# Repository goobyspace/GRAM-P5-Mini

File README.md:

# GRAM Slim

# Brook Version

This repo contains within the folder Gram FGC -> v1.brook, an edited version based on the v1.2 version that uses a brook P5-mini board. It's also edited specifically for a layout I find more comfortable, with the thumb button on the right hand outwards, instead of tucked under.

The PCB was made with heavy inspiration of the V1.2 PCB by [Quark](https://twitter.com/quark_works) as well as the (Flatbox)[https://github.com/jfedor2/flatbox], which includes an example of a Brook mini PCB & it's footprint in the rev3 version. Although the flatbox uses the PS3/PS4 mini, the pinout for the P5 mini has stayed the same.

This project was entirely for my own personal reasons, wanting the split thumb buttons & the pinky buttons on both sides moved down, as well as easier PS5 support (Hence the brook P5 mini). Don't expect the world from the PCB in here, it was my very first time learning Kicad, and if you want to take inspiration for your own edits, I heavily recommend this [stream](https://www.youtube.com/watch?v=zCp_-3P3b8c) by Quark. Though any keyboard PCB tutorials are a good start.

The gram top panel in the panels folder of V1.brook has also been edited to match the new button layout. The reason for choosing the V1.2 version was simply that it's the one I already owned, and I found it a lot easier to figure out what I was looking at with a dissected example next to me.

# Gram
For an ordering & assembly guide, check out the [GRAM-SLIM](https://github.com/GRAMCTRL/GRAM-SLIM) repo that this one was forked from!

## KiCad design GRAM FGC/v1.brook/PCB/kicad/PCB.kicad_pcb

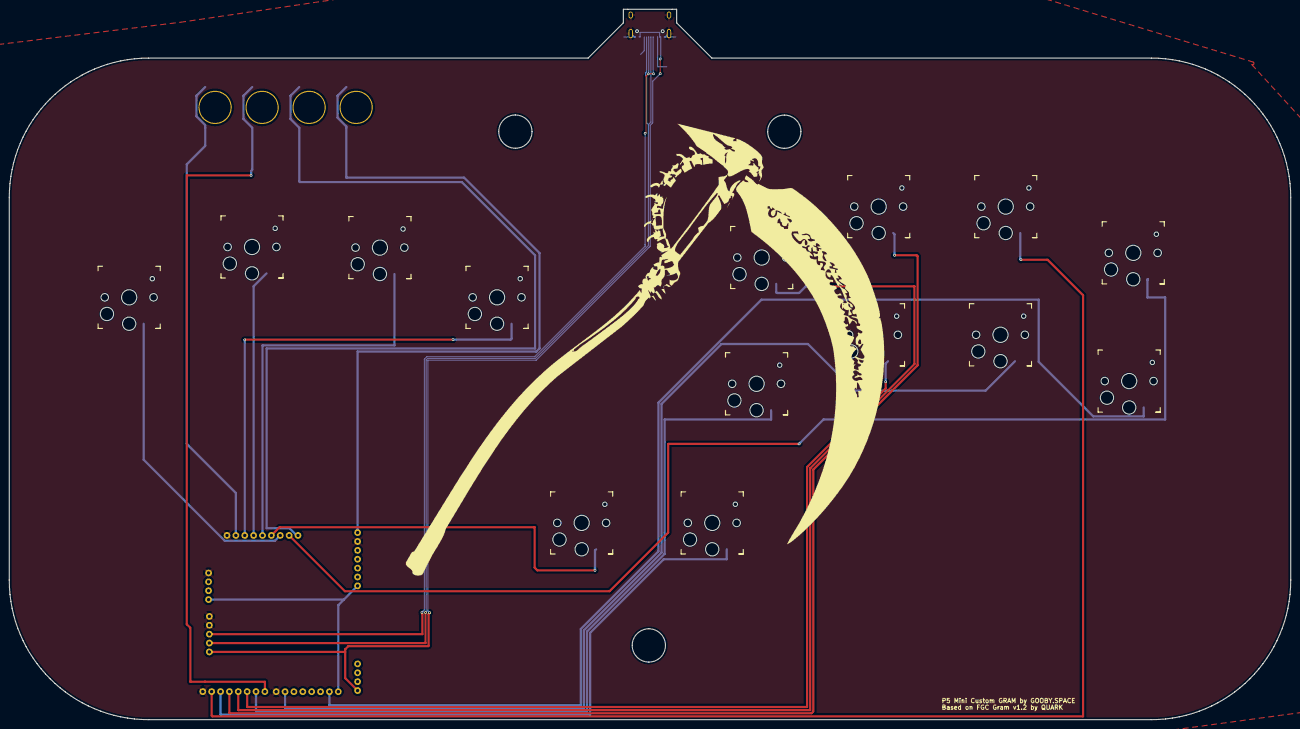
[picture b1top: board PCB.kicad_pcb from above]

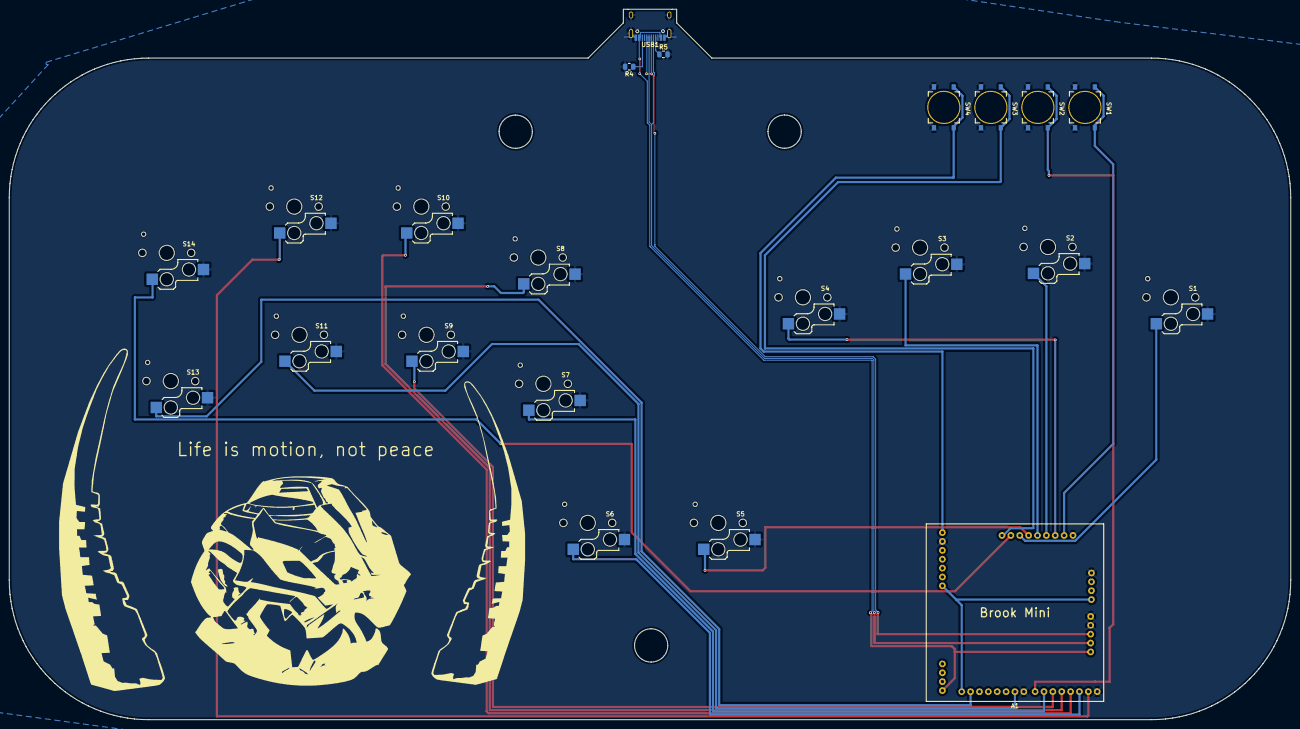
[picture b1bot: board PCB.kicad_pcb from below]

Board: 2 copper layers, 288.8 x 160.1 mm, 22 parts (4 on the bottom side), 24 nets.

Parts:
A1: Brook_PS3PS4_PCBA
R4, R5: 5.1k; R_0805_2012Metric
S1, S2, S3, S4, S5, S6, S7, S8, S9, S10, S11, S12, S13, S14: Keyswitch; Kailh_socket_PG1350
SW1, SW2, SW3, SW4: SW_Push; RT3301AF260Q
USB1: HRO-TYPE-C-31-M-12

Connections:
+5V: A1.35 (VDD_5V), USB1.2 (VBUS), USB1.11 (VBUS)
Circle: A1.14 (CIRCLE), S9.1
Cross: A1.15 (CROSS), S7.1
D+: A1.28 (USB_D+), USB1.6 (DP1), USB1.8 (DP2)
D-: A1.29 (USB_D-), USB1.5 (DN2), USB1.7 (DN1)
Down: A1.5 (D_Down), S3.1
GND: A1.1 (GND), R4.2, R5.2, S1.2, S2.2, S3.2, S4.2, S5.2, S6.2, S7.2, S8.2, S9.2, S10.2, S11.2, S12.2, S13.2, S14.2, SW1.1, SW2.1, SW3.1, SW4.1, USB1.1 (GND), USB1.12 (GND), USB1.13 (SHIELD)
L1: A1.8 (L1), S14.1
L2: A1.22 (L2), S13.1
L3: A1.7 (L3), S1.1
Left: A1.4 (D_Left), S2.1
unnamed: R5.1, USB1.4 (CC1)
unnamed: R4.1, USB1.10 (CC2)
Options: A1.2 (Options), SW1.2
PS: A1.9 (PS_Key), SW3.2
R1: A1.10 (R1), S12.1
R2: A1.17 (R2), S11.1
R3: A1.11 (R3), S6.1
Right: A1.3 (D_Right), S4.1
Share: A1.16 (SHARE), SW2.2
Square: A1.13 (SQUARE), S8.1
Touchpad: A1.23 (TPKEY), SW4.2
Triangle: A1.12 (TRIANGLE), S10.1
Up: A1.6 (D_Up), S5.1

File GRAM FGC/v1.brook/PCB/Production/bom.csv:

Designator,Footprint,Quantity,Value,LCSC Part #
A1,Brook_PS3PS4_PCBA,1,Brook_PS3PS4_PCBA,
"R4, R5",0805,2,5.1k,C27834
"S1, S10, S11, S12, S13, S14, S2, S3, S4, S5, S6, S7, S8, S9",Kailh_socket_PG1350,14,Keyswitch,
"SW1, SW2, SW3, SW4",RT3301AF260Q,4,SW_Push,
USB1,HRO-TYPE-C-31-M-12,1,HRO-TYPE-C-31-M-12,C165948

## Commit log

2024-12-13 Updated with screwless and FGC
2024-12-13 Added warning about new non-DIY-friendly parts
2025-01-31 Add base files
2025-01-31 Fixed connections, top panel & gerbers
2025-05-05 Added flatbox USB style
2025-05-12 Final working version
